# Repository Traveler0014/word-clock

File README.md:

# Word Clock 字钟项目

QLOCKTWO-style English word clock — ESP32-C5 + WS2812B (114 LEDs), built with Rust (esp-idf-svc on ESP-IDF v5.5.1), parametric 3D-printed enclosure.

QLOCKTWO 风格英文字钟：11×10 字母阵 + 4 角分钟点，ESP32-C5 + WS2812B（60灯/米），结构件 3D 打印。

**当前状态：Phase A-MVP 实机已点亮**（自检 → WiFi → SNTP → 每分钟刷新全链路跑通，2026-08）。

## 目录结构

| 路径 | 内容 |
|---|---|
| `firmware/` | Rust 固件（esp-idf-svc / std on IDF v5.5.1）+ 可宿主测试的 `wordclock-core` |
| `enclosure/` | 3D 打印结构件（OpenSCAD 参数化源码） |
| `hardware/` | 灯板 PCB（KiCad 原理图 + PCB + Gerber + 生成脚本） |
| `docs/` | 项目文档（见下） |
| `tools/` | 宿主机工具：串口嗅探、帧校验、动效实验台（`anim_lab.py`） |
| `AGENTS.md` | AI agent 快速上手指南 |

## 文档导航

| 文档 | 内容 |
|---|---|
| [docs/roadmap.md](docs/roadmap.md) | 路线图与当前进度 |
| [docs/development.md](docs/development.md) | 开发指南：环境搭建、编译烧录、日志调试、踩坑记录 |
| [docs/wiring.md](docs/wiring.md) | 接线图：供电/数据/灯链布局/验证阶段接线 |
| [docs/bom.md](docs/bom.md) | 物料清单与功率预算 |
| [docs/animation.md](docs/animation.md) | 灯板动效设计：克制的语法、状态→母题表、星场算法、α↔8bit 换算 |
| [docs/led-pcb.md](docs/led-pcb.md) | 灯板 PCB 方案评估：尺寸/pitch 决策、电学设计、与 ESP32-C5 连接 |
| [hardware/README.md](hardware/README.md) | 灯板 PCB 设计文件说明（KiCad 原理图/PCB/Gerber/生成脚本） |
| [firmware/README.md](firmware/README.md) | 固件模块结构与版本锁定 |
| [enclosure/README.md](enclosure/README.md) | 结构件参数与打印说明 |

## 快速开始

```bash
cd firmware && source env.sh                     # 环境（一次性）
cargo test -p wordclock-core --target x86_64-unknown-linux-gnu   # 逻辑层测试（宿主机）
```

编译刷写与日志调试见 [docs/development.md](docs/development.md)。

## License

[MIT](LICENSE)

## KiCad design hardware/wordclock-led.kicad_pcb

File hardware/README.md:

# hardware/ — 灯板 PCB 设计（KiCad）

把原方案的 10 行灯条 + 27 处行间飞线，替换成**单块 192×192mm 的 LED 面板 PCB**。
含**原理图 + PCB + Gerber + 预览图 + 可复现的生成脚本**。

> 方案背景与取舍见 [`../docs/led-pcb.md`](../docs/led-pcb.md)。
> 本目录是其中「方案 A：灯板 + 现有 ESP32-C5-DevKitC」的具体实现。

## 文件

| 文件 | 内容 |
|---|---|
| `wordclock-led.kicad_pro` | KiCad 工程 |
| `wordclock-led.kicad_sch` | 原理图（平坦单页 A1：114 颗灯 + 电平转换 + 电源/接口） |
| `wordclock-led.kicad_pcb` | PCB（2 层，已铺铜填充） |
| `wordclock-led-sch.pdf` | 原理图 PDF（便于评审） |
| `gen/gen_sch.py` | 原理图生成脚本（纯标准库，任意 python3） |
| `gen/gen_pcb.py` | PCB 生成脚本（需 KiCad 自带 python + pcbnew） |
| `preview/pcb_top.png` / `pcb_bottom.png` | 3D 预览 |
| `fab/*` | Gerber + 钻孔（F.Cu/B.Cu/Mask/Paste/Silk/Edge + drl + job） |

> `fab/pcba.step` 不入库（`.gitignore` 已排除）：它与 `pcba.step` 字节完全一致，
> 只是给「自洽的 fab 包」用。要直接丢给板厂/贴片厂时手动拷：`cp pcba.step fab/`。

## 板子规格

| 项 | 值 |
|---|---|
| 尺寸 / 层数 | 192.0 × 192.0 mm，2 层，1.6 mm，1oz（建议 2oz 或限制亮度） |
| 灯 | 114 × WS2812B 5050（110 字母阵 11×10 + 4 角点） |
| 灯距 pitch | **15.0 mm**（字母阵 165×150，居中留边 13.5 / 21） |
| 角点 | 距板角 7 mm（腔/窗由结构件做，φ11 / φ5） |
| 数据链 | 蛇形（行 0 左→右，奇数行反向），链尾 109 在左下；角点按周长环 110→111→112→113。**原理图用显式串联导线画出**（奇数行 `mirror y` 让 DIN/DOUT 朝向链方向，VDD/VSS 保持上下） |
| 走线 | 数据走线全程**无直角**：转弯一律 45° 倒角 |
| 电源 | 顶层 **GND 铺铜区**，底层 **+5V 平面**；每颗 LED/电容就近打过孔到 +5V |
| 去耦 | 每颗灯 1 × 100nF 0402（C1–C114），入口 1000µF + 22µF + 100nF |
| 电平转换 | U1 = 74AHCT1G125（SOT-23-5，5V 供电），输出串 R1 = 33Ω |
| 安装孔 | 4 × M3（四边中点，和原外壳螺丝位一致） |
| 丝印 | 板名、`5V IN (J2)` / `ESP32-C5 (J1)`、+5V/GND |

## 与 ESP32-C5 的连接

```
ESP32-C5-DevKitC-1                灯板 (J1)                板上
  GPIO4 ── 杜邦/JST 4pin DATA ──► J1.3 ──► U1.A ── 74AHCT1G125(5V) ──► R1(33Ω) ──► D1.DIN
  GND   ────────────────────────► J1.2/4 (GND)
  5V    ◄─────────────────────── J1.1 (仅当 JP1 短接)
                                   J2 = 5V/3A 外部电源输入（5V,5V,GND,GND）
```

| 连接器 | 引脚 | 网络 | 说明 |
|---|---|---|---|
| **J1**（接 DevKitC） | 1 | `/+5V_DEV` | 经 JP1 可选给开发板供 5V |
| | 2, 4 | `GND` | |
| | 3 | `/DIN_IN` | 来自 C5 `GPIO4` 的 3.3V 数据 |
| **J2**（电源输入） | 1, 2 | `+5V` | 5V/3A，双针并联 |
| | 3, 4 | `GND` | |
| **JP1**（焊桥） | 1–2 | `+5V` ↔ `/+5V_DEV` | **默认断开**；短接则灯板 5V 反给开发板 |

- **开发期**：DevKitC 用 USB 供电时 **JP1 保持断开**（否则双电源互灌）；两者务必共地（J1.2/4）。
- **成品**：外部 5V 接 J2，JP1 短接，由灯板同时给开发板供电，或继续让开发板独立供电。
- 数据电平：板载 74AHCT125 已做 3.3V→5V，**不要再外接电平转换**。

> 若后续要出「集成版 v2」（ESP32-C5-WROOM-1 直接上板），参考 `../docs/led-pcb.md` §5 方案 B：
> 原生 USB-Serial-JTAG（IO13/14）+ IO4(RMT) + IO1(ADC 光敏) + IO23/24(I2C)，
> 天线强烈建议用 WROOM-1U 外置，USB 控制台需改 sdkconfig。

## ⚠ 元件高度与勘误

- 正面最高元件：**C117 电解 11.5mm** > 排针 8.5mm > C116 2.52mm > 灯珠 1.61mm。
  结构件按 14mm 格栅净高设计。完整实测表见 [`../docs/pcba-heights.md`](../docs/pcba-heights.md)。
- **J1/J2 已换料**：原 BOM 的 C492419（XFCN PZ254V-12-4P）是**双排 2×2**，插不进
  `PinHeader_1x04`；已改用 **LCSC C19190970 = HDGC HDGCPH-PZ01-04**（单排 1×4，金镀），
  板面高 **8.54 mm**。
- STEP 外包络是 192×**202**（上下各 ~4.85mm 工艺边），实际板子 **192×192**。

## 固件

**无需改动**：仍 GPIO4、仍 114 颗、蛇形索引与 `wordclock-core::xy_to_index` 一致。
PCB 网络名与原理图完全一致（`/D0…/D113`、`/DOUT`、`/DIN_IN`、`/S1`、`/+5V_DEV`、`+5V`、`GND`），
所以在 KiCad 里「从原理图更新 PCB」不会断开已布好的线。

角点顺序在板上是 `110 左下 → 111 右下 → 112 右上 → 113 左上`。
固件只看「点亮前 n 颗」，功能不受影响；若想 `minute=1` 固定点某角，改 `Frame::dots()` 一行即可
（原 `docs/wiring.md` 的 110~113 标注需同步修正）。

## 校验记录

- **ERC**：0 error / 0 warning
- **DRC**：0 violation / 0 未连接；走线无直角（转弯均 45°）
- **网络一致性**：原理图 netlist 与 PCB 焊盘网络逐网比对，120 网 **0 mismatch**
- **串联链**：`/D0…/D113`、`/DOUT` 逐节校验（`D{i}.DOUT → D{i+1}.DIN`）全部正确
- **Gerber/钻孔**：`kicad-cli` 导出成功

重新校验（KiCad 10 命令行）：

```bash
kicad-cli sch erc   --severity-error wordclock-led.kicad_sch
kicad-cli pcb drc   --severity-error wordclock-led.kicad_pcb
kicad-cli pcb export gerbers -o fab/ -l "F.Cu,B.Cu,F.Mask,B.Mask,F.Paste,B.Paste,F.Silkscreen,B.Silkscreen,Edge.Cuts" wordclock-led.kicad_pcb
kicad-cli pcb export drill   -o fab/ wordclock-led.kicad_pcb
```

## 重新生成

```
hardware/
├── gen/gen_sch.py     # 任意 python3（Linux 亦可），读 KiCad 符号库
└── gen/gen_pcb.py     # 必须用 KiCad 自带 python（带 pcbnew 模块）
```

```bash
cd hardware
python3 gen/gen_sch.py                                   # 生成 .kicad_sch
"C:/Program Files/KiCad/10.0/bin/python.exe" gen/gen_pcb.py   # 生成 .kicad_pcb（含铺铜）
```

脚本里的几何参数（板尺寸、pitch、元件坐标、走线）都在文件顶部，改完全局重跑即可。
两脚本自动探测 KiCad 安装路径（Windows `D:\...` 或 WSL `/mnt/d/...`）。
每次生成 UUID 随机，故与已提交版本会有 diff，属正常。

> `gen_pcb.py` 的铺铜需要「保存→重新加载→填充→再保存」的往返：
> 无头模式下直接对新建 board 调 `ZONE_FILLER` 会崩（已在脚本内处理）。

## 打样 / 装配注意

- 2 层 192×192 已能覆盖当前电流（实测 <0.5A）；全白跑满 6.8A 时请用 2oz 或限亮。
- 每颗 5050 的 GND 焊盘**实心**连到 GND 铺铜（利于散热与载流）；返修时热风要够功率。
- C117（1000µF 直立电解）在板正面顶边（146, 11.5），高度约 12mm。
- 控制区（顶边 y≈3..19）元件在**正面**：结构件需在该处留凹槽/让位，
  或把控制区整体移到板背（+5V 平面留 keepout 即可）。见「待决」。
- 建议先打 **1 片** 验证：先只上 5V 测短路/静态电流，再用现有固件自检全链。

## 待决 / 风险

1. **"200×200"口径**：若指含外壳的成品，PCB 可再缩到 ~192→实际外框 200；当前 PCB 192 + 4mm 壁 ≈ 200×200，正好。
2. **控制区位置**：现放正面顶边，结构件要配合；若想更干净可移到背面。
3. **角点顺序**：如需 `minute=1 → 左上`，改固件映射（1 行）。
4. **散热/密封**：密封腔 + 1/4 限亮预计 OK；全白需通风。
5. **是否做集成版 v2**（C5 上板）：见 `../docs/led-pcb.md` §5。

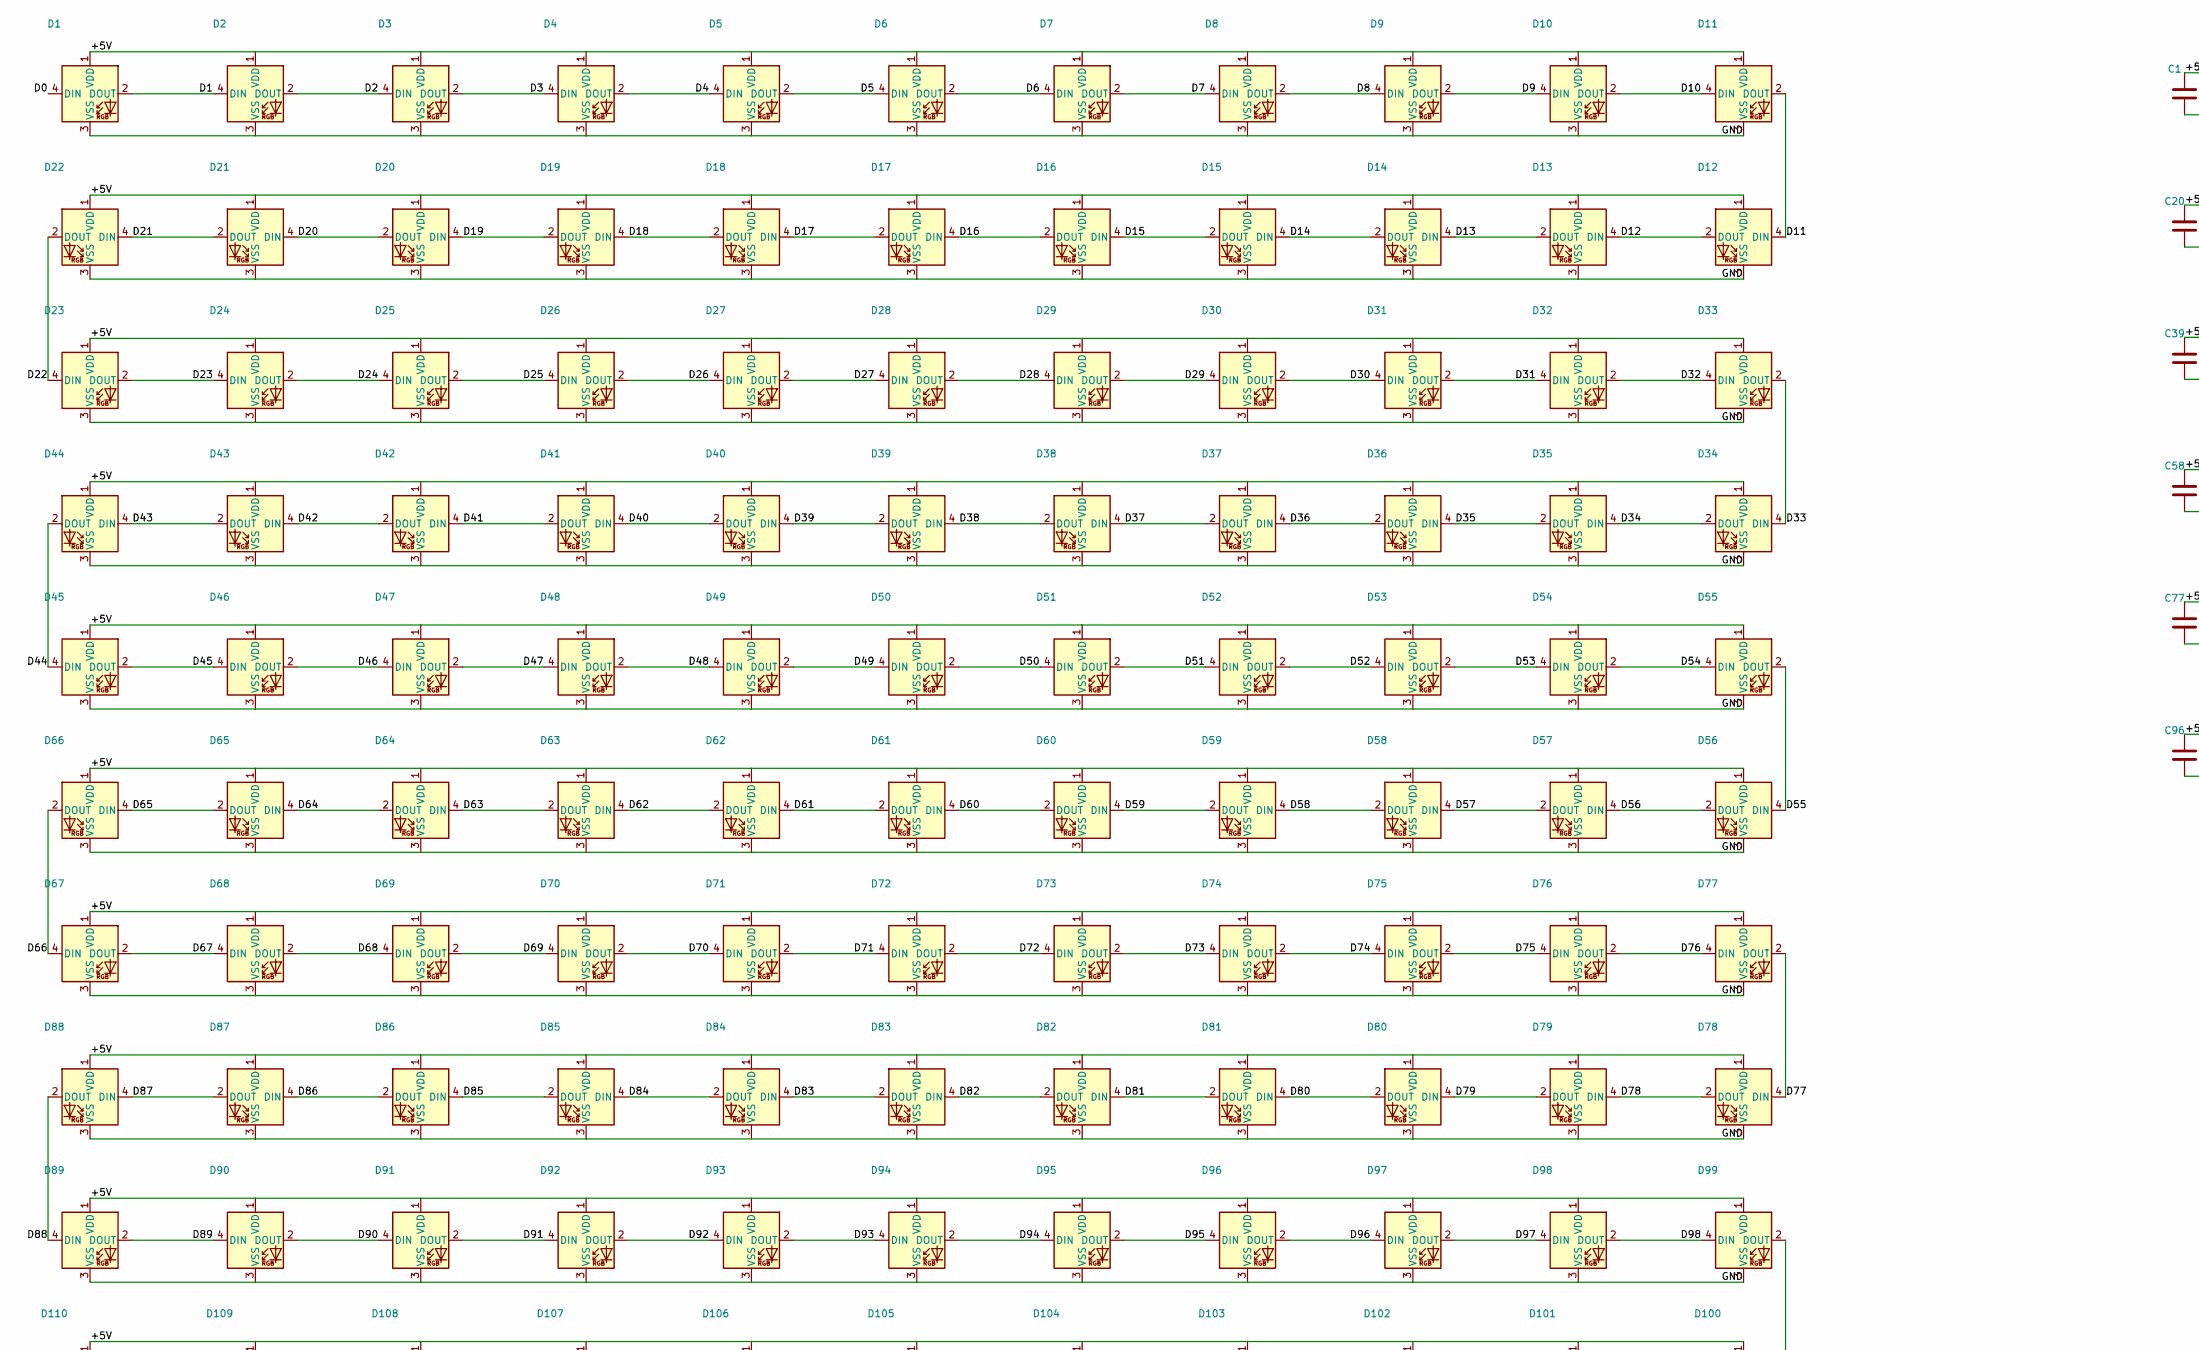
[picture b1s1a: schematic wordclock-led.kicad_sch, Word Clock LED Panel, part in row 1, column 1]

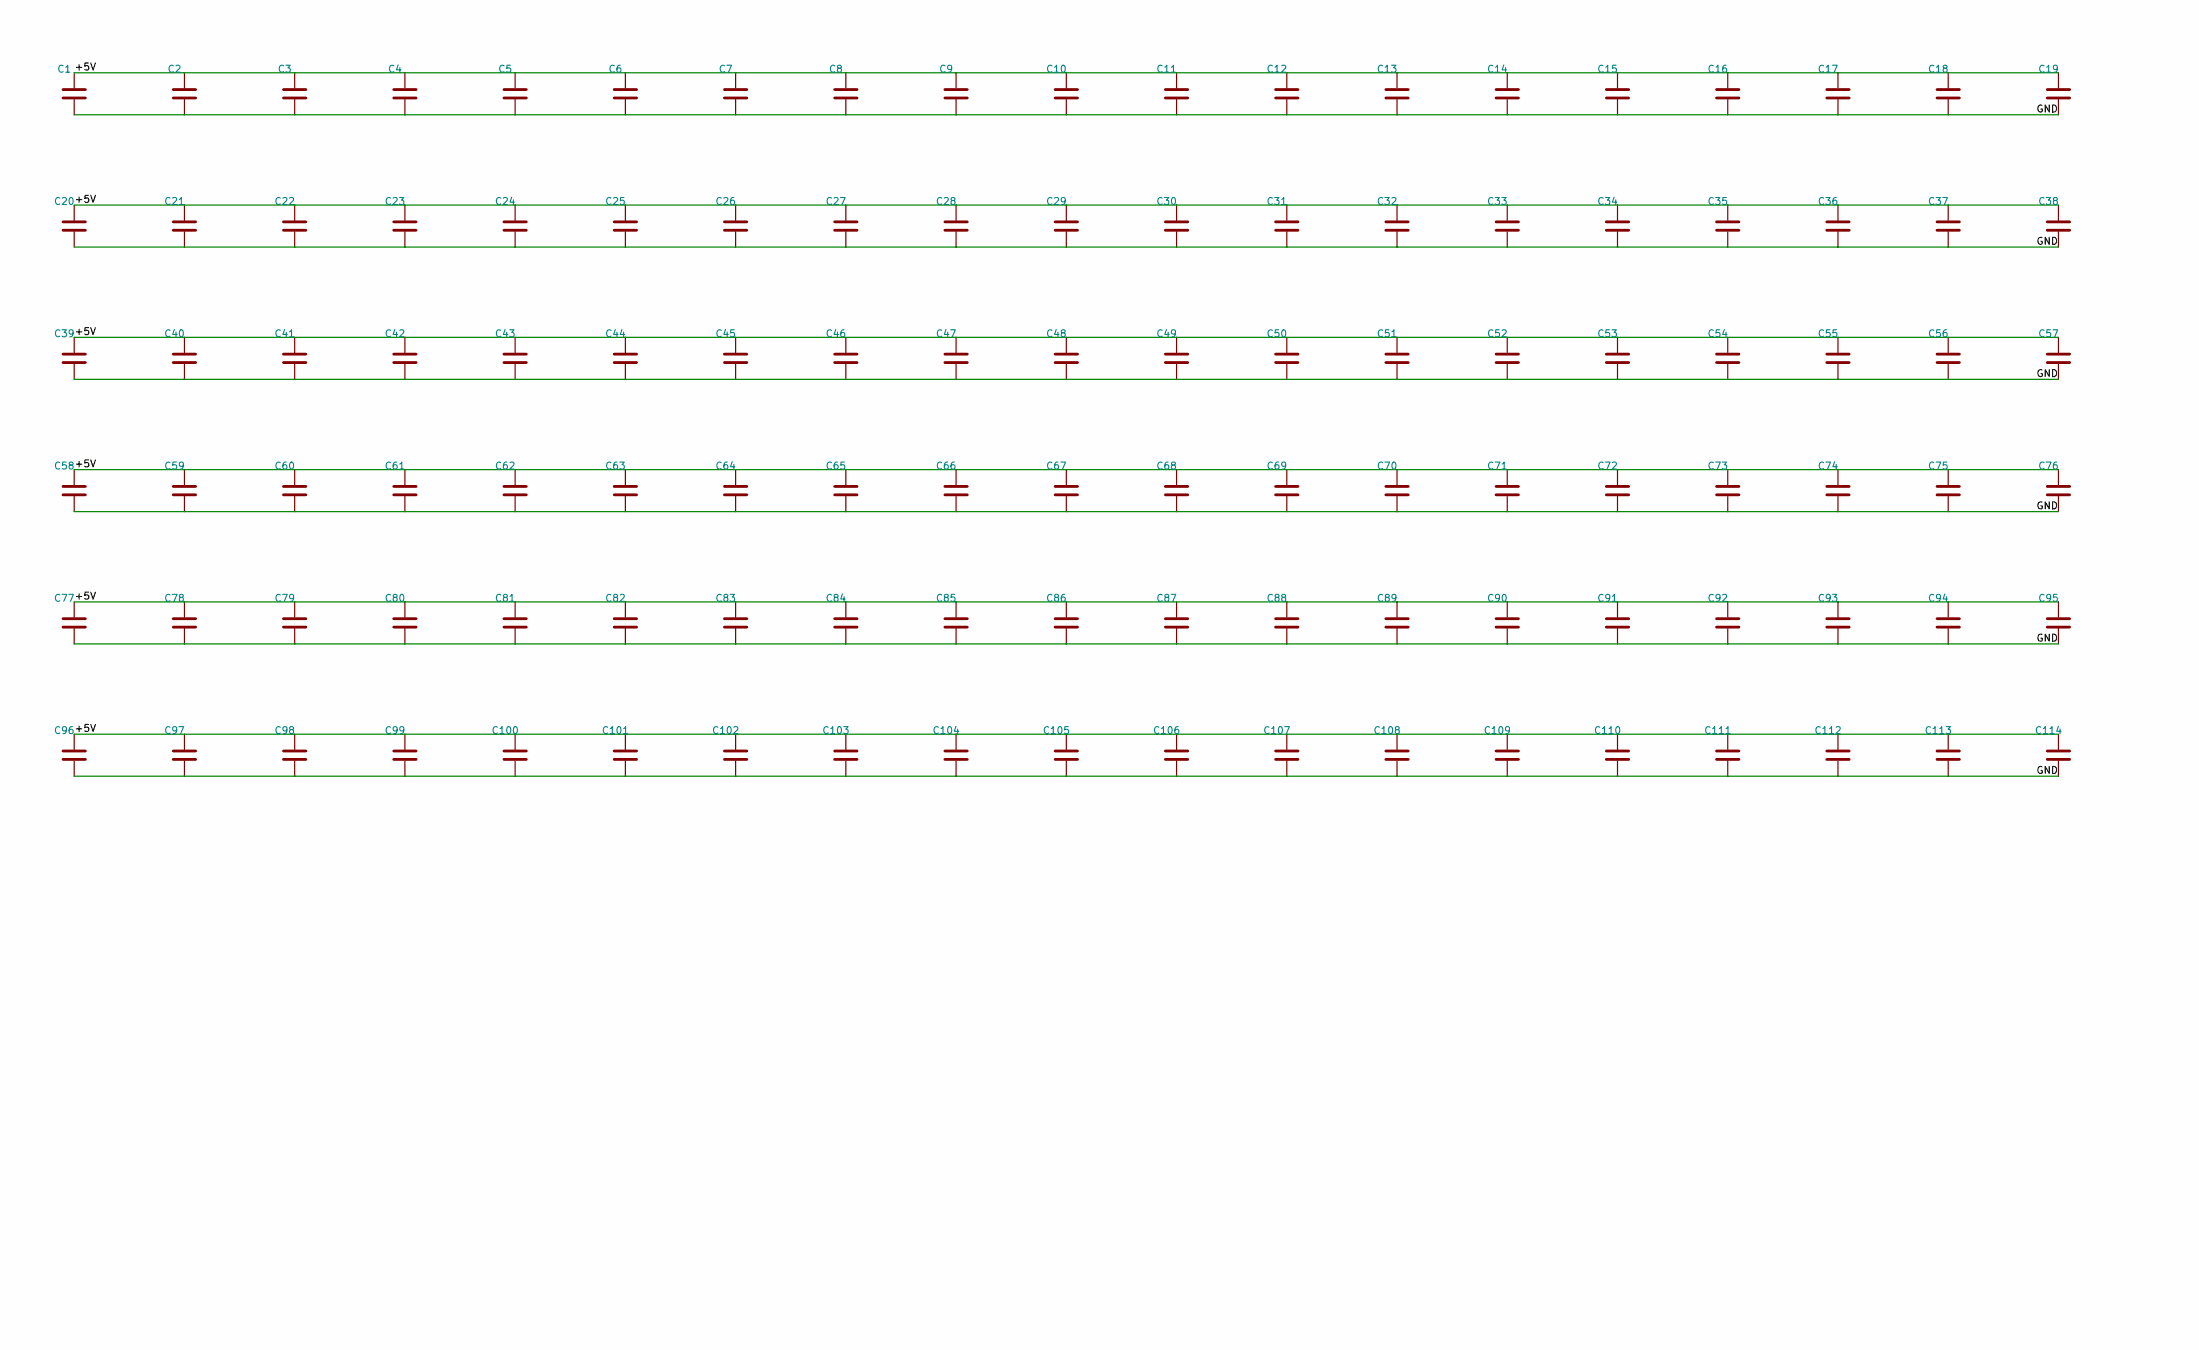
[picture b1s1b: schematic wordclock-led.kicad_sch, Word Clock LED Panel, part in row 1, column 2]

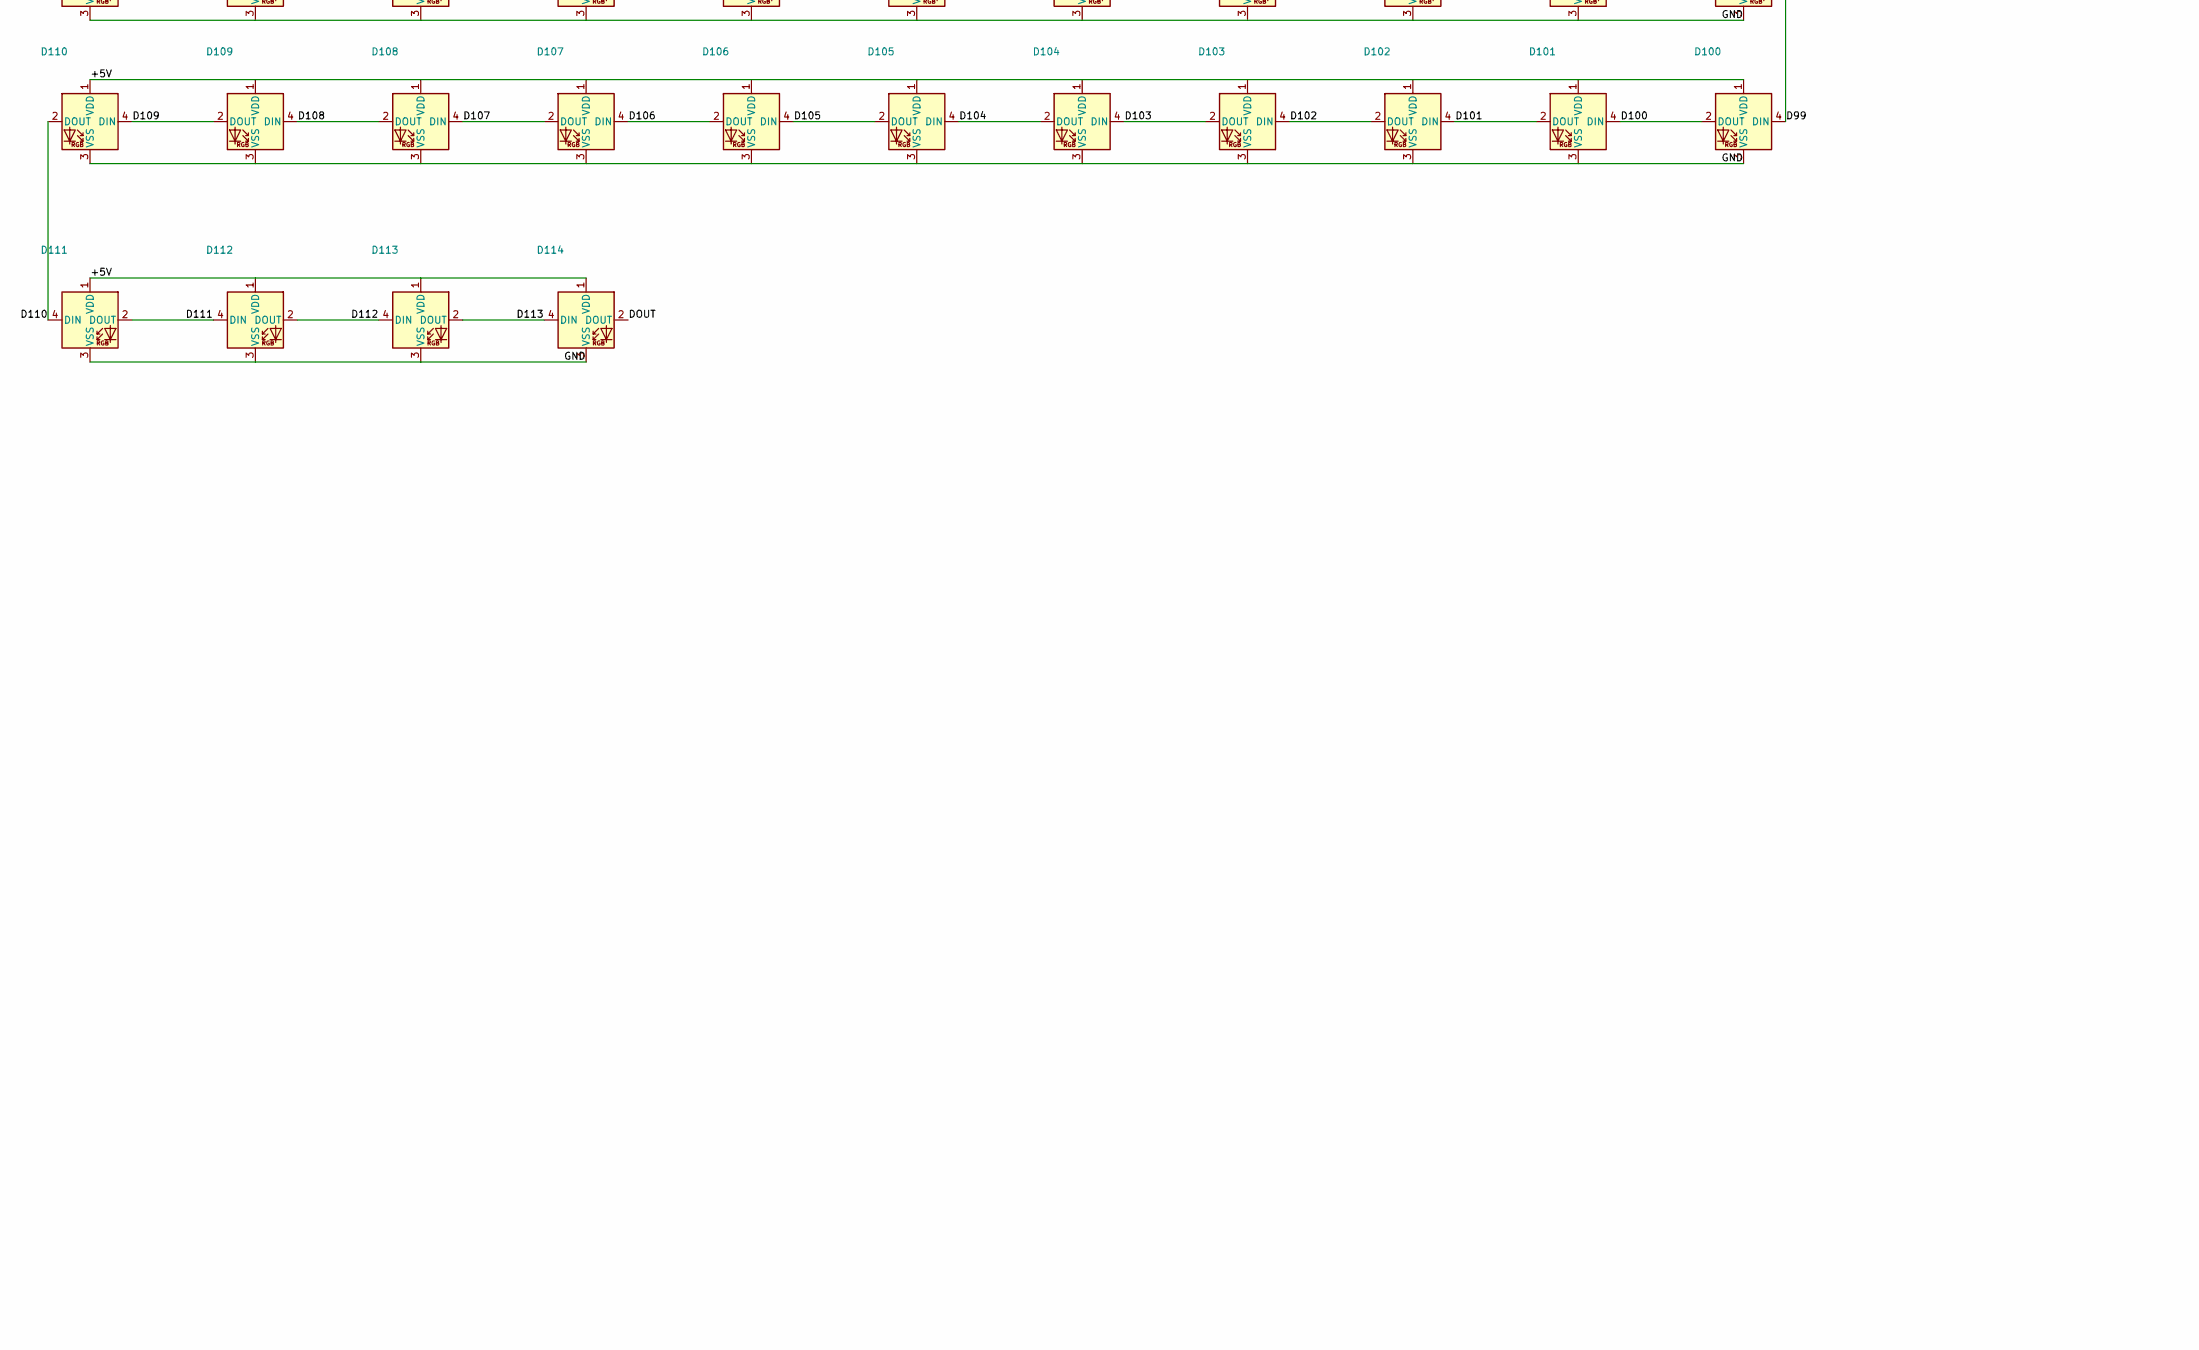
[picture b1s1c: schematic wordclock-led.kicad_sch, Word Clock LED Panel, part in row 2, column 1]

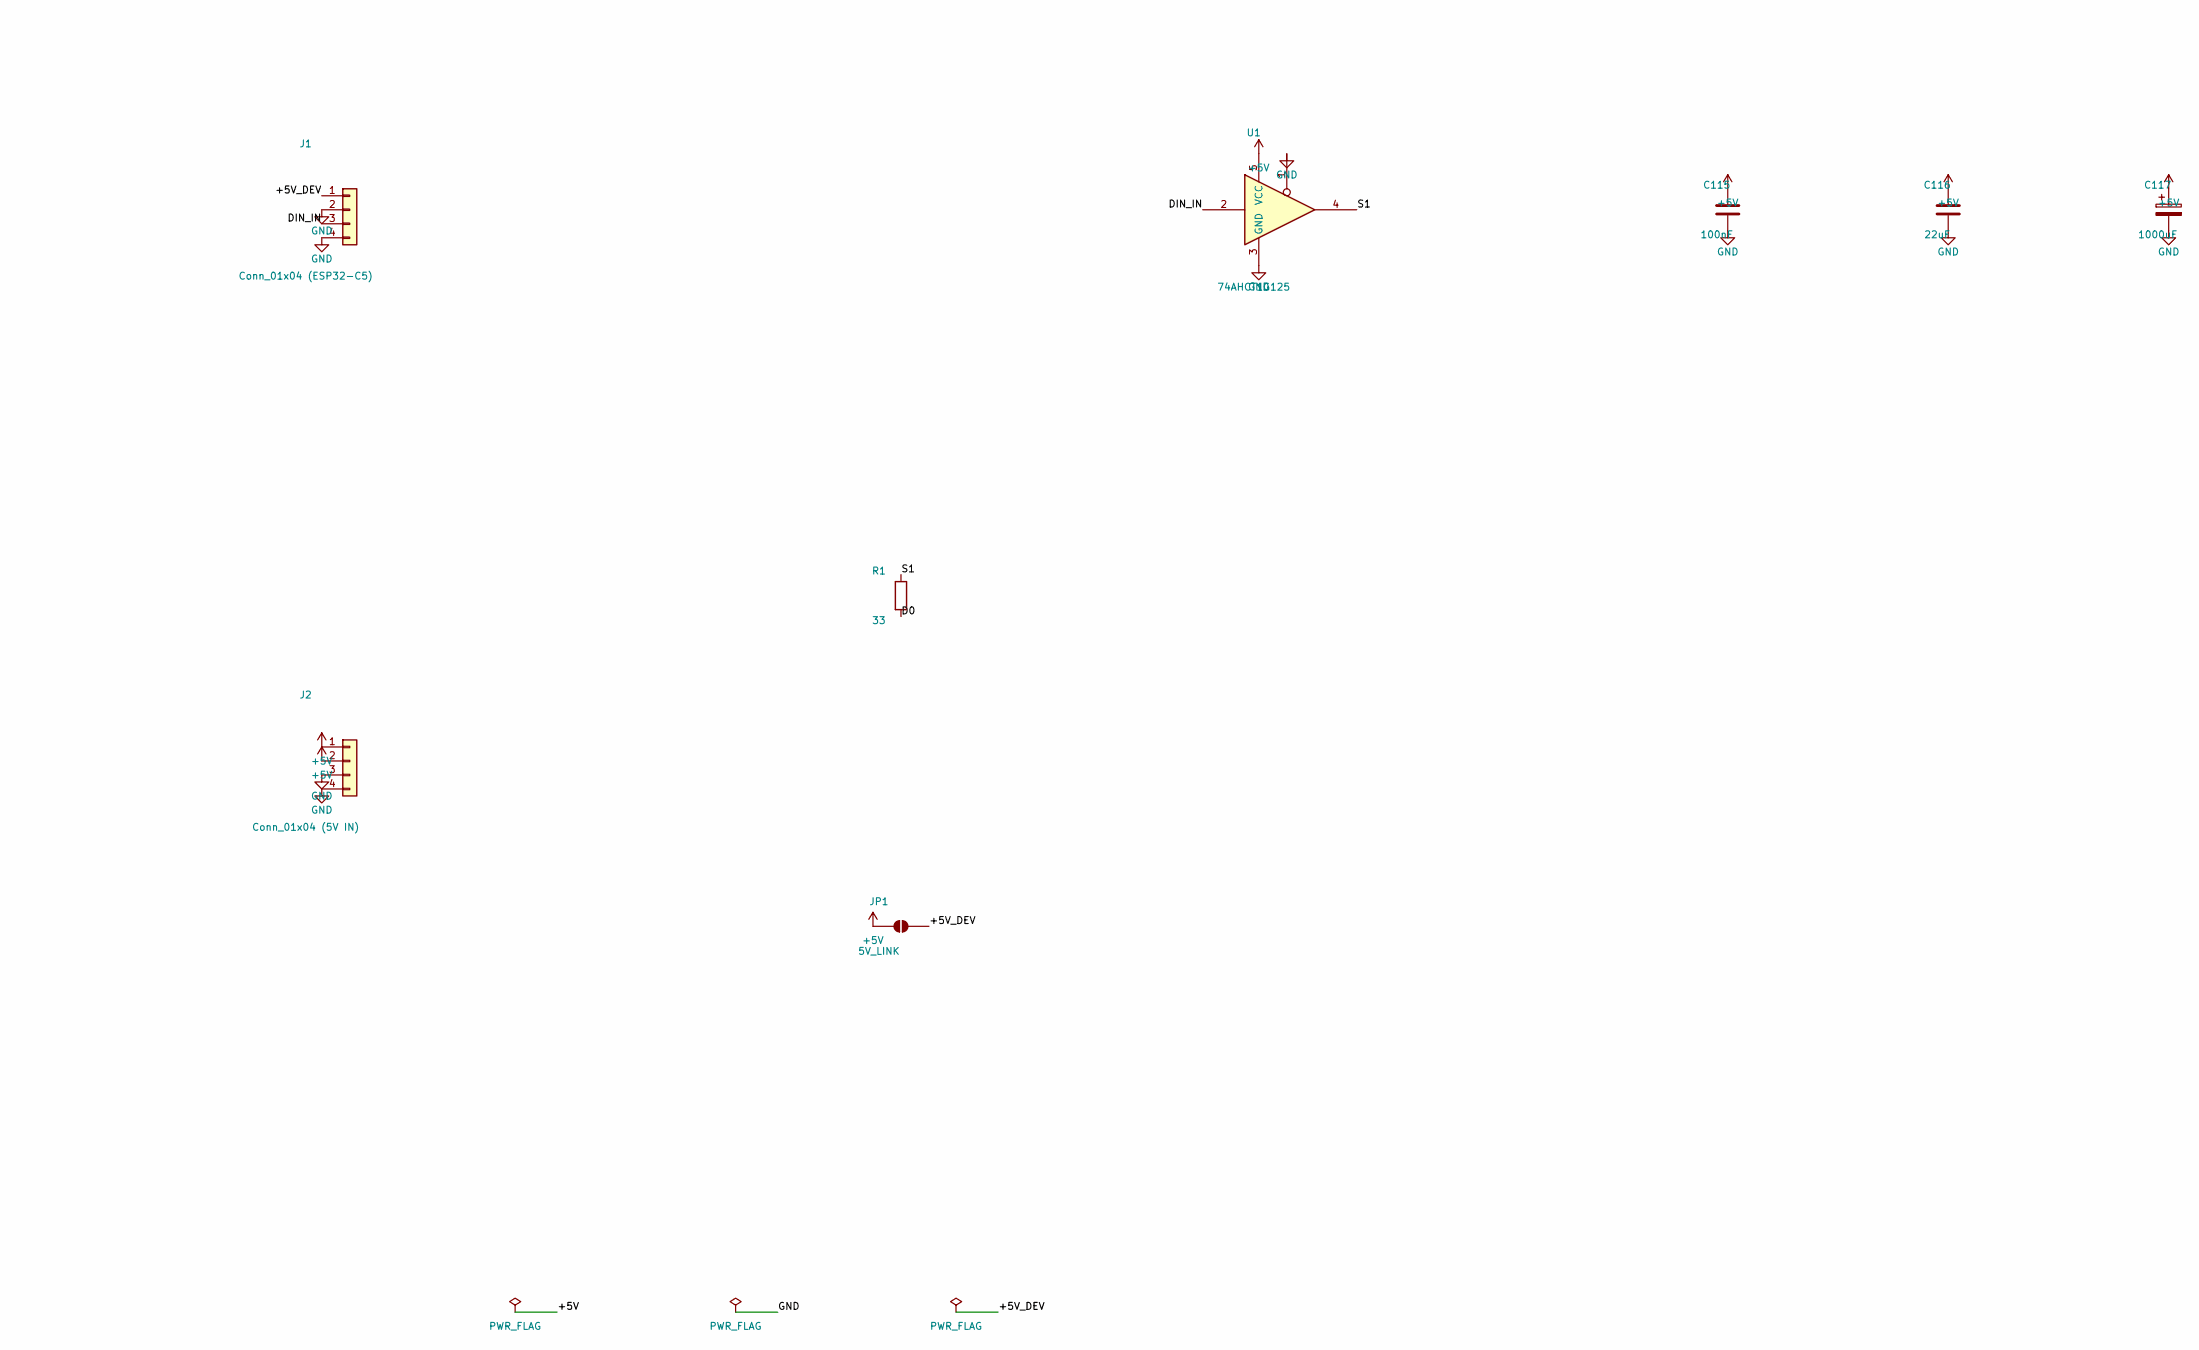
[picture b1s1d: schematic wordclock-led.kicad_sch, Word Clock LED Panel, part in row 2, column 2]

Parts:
C1, C2, C3, C4, C5, C6, C7, C8, C9, C10, C11, C12, C13, C14, C15, C16, C17, C18, C19, C20, C21, C22, C23, C24, C25, C26, C27, C28, C29, C30, C31, C32, C33, C34, C35, C36, C37, C38, C39, C40, C41, C42, C43, C44, C45, C46, C47, C48, C49, C50, C51, C52, C53, C54, C55, C56, C57, C58, C59, C60, C61, C62, C63, C64, C65, C66, C67, C68, C69, C70, C71, C72, C73, C74, C75, C76, C77, C78, C79, C80, C81, C82, C83, C84, C85, C86, C87, C88, C89, C90, C91, C92, C93, C94, C95, C96, C97, C98, C99, C100, C101, C102, C103, C104, C105, C106, C107, C108, C109, C110, C111, C112, C113, C114: 100nF; C_0402_1005Metric
C115: 100nF; C_0603_1608Metric
C116: 22uF; C_1210_3225Metric
C117: 1000uF; CP_Radial_D10.0mm_P5.00mm
D1, D2, D3, D4, D5, D6, D7, D8, D9, D10, D11, D12, D13, D14, D15, D16, D17, D18, D19, D20, D21, D22, D23, D24, D25, D26, D27, D28, D29, D30, D31, D32, D33, D34, D35, D36, D37, D38, D39, D40, D41, D42, D43, D44, D45, D46, D47, D48, D49, D50, D51, D52, D53, D54, D55, D56, D57, D58, D59, D60, D61, D62, D63, D64, D65, D66, D67, D68, D69, D70, D71, D72, D73, D74, D75, D76, D77, D78, D79, D80, D81, D82, D83, D84, D85, D86, D87, D88, D89, D90, D91, D92, D93, D94, D95, D96, D97, D98, D99, D100, D101, D102, D103, D104, D105, D106, D107, D108, D109, D110, D111, D112, D113, D114: WS2812B; LED_WS2812B_PLCC4_5.0x5.0mm_P3.2mm
J1: Conn_01x04 (ESP32-C5); PinHeader_1x04_P2.54mm_Vertical
J2: Conn_01x04 (5V IN); PinHeader_1x04_P2.54mm_Vertical
JP1: 5V_LINK; SolderJumper-2_P1.3mm_Open_RoundedPad1.0x1.5mm
R1: 33; R_0603_1608Metric
U1: 74AHCT1G125; SOT-23-5

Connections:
+5V: C1.1, C2.1, C3.1, C4.1, C5.1, C6.1, C7.1, C8.1, C9.1, C10.1, C11.1, C12.1, C13.1, C14.1, C15.1, C16.1, C17.1, C18.1, C19.1, C20.1, C21.1, C22.1, C23.1, C24.1, C25.1, C26.1, C27.1, C28.1, C29.1, C30.1, C31.1, C32.1, C33.1, C34.1, C35.1, C36.1, C37.1, C38.1, C39.1, C40.1, C41.1, C42.1, C43.1, C44.1, C45.1, C46.1, C47.1, C48.1, C49.1, C50.1, C51.1, C52.1, C53.1, C54.1, C55.1, C56.1, C57.1, C58.1, C59.1, C60.1, C61.1, C62.1, C63.1, C64.1, C65.1, C66.1, C67.1, C68.1, C69.1, C70.1, C71.1, C72.1, C73.1, C74.1, C75.1, C76.1, C77.1, C78.1, C79.1, C80.1, C81.1, C82.1, C83.1, C84.1, C85.1, C86.1, C87.1, C88.1, C89.1, C90.1, C91.1, C92.1, C93.1, C94.1, C95.1, C96.1, C97.1, C98.1, C99.1, C100.1, C101.1, C102.1, C103.1, C104.1, C105.1, C106.1, C107.1, C108.1, C109.1, C110.1, C111.1, C112.1, C113.1, C114.1, C115.1, C116.1, C117.1, D1.1 (VDD), D2.1 (VDD), D3.1 (VDD), D4.1 (VDD), D5.1 (VDD), D6.1 (VDD), D7.1 (VDD), D8.1 (VDD), D9.1 (VDD), D10.1 (VDD), D11.1 (VDD), D12.1 (VDD), D13.1 (VDD), D14.1 (VDD), D15.1 (VDD), D16.1 (VDD), D17.1 (VDD), D18.1 (VDD), D19.1 (VDD), D20.1 (VDD), D21.1 (VDD), D22.1 (VDD), D23.1 (VDD), D24.1 (VDD), D25.1 (VDD), D26.1 (VDD), D27.1 (VDD), D28.1 (VDD), D29.1 (VDD), D30.1 (VDD), D31.1 (VDD), D32.1 (VDD), D33.1 (VDD), D34.1 (VDD), D35.1 (VDD), D36.1 (VDD), D37.1 (VDD), D38.1 (VDD), D39.1 (VDD), D40.1 (VDD), D41.1 (VDD), D42.1 (VDD), D43.1 (VDD), D44.1 (VDD), D45.1 (VDD), D46.1 (VDD), D47.1 (VDD), D48.1 (VDD), D49.1 (VDD), D50.1 (VDD), D51.1 (VDD), D52.1 (VDD), D53.1 (VDD), D54.1 (VDD), D55.1 (VDD), D56.1 (VDD), D57.1 (VDD), D58.1 (VDD), D59.1 (VDD), D60.1 (VDD), D61.1 (VDD), D62.1 (VDD), D63.1 (VDD), D64.1 (VDD), D65.1 (VDD), D66.1 (VDD), D67.1 (VDD), D68.1 (VDD), D69.1 (VDD), D70.1 (VDD), D71.1 (VDD), D72.1 (VDD), D73.1 (VDD), D74.1 (VDD), D75.1 (VDD), D76.1 (VDD), D77.1 (VDD), D78.1 (VDD), D79.1 (VDD), D80.1 (VDD), D81.1 (VDD), D82.1 (VDD), D83.1 (VDD), D84.1 (VDD), D85.1 (VDD), D86.1 (VDD)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
/+5V_DEV: J1.1, JP1.2 (B)
/D0: D1.4 (DIN), R1.2
/D1: D1.2 (DOUT), D2.4 (DIN)
/D2: D2.2 (DOUT), D3.4 (DIN)
/D3: D3.2 (DOUT), D4.4 (DIN)
/D4: D4.2 (DOUT), D5.4 (DIN)
/D5: D5.2 (DOUT), D6.4 (DIN)
/D6: D6.2 (DOUT), D7.4 (DIN)
/D7: D7.2 (DOUT), D8.4 (DIN)
/D8: D8.2 (DOUT), D9.4 (DIN)
/D9: D9.2 (DOUT), D10.4 (DIN)
/D10: D10.2 (DOUT), D11.4 (DIN)
/D11: D11.2 (DOUT), D12.4 (DIN)
/D12: D12.2 (DOUT), D13.4 (DIN)
/D13: D13.2 (DOUT), D14.4 (DIN)
/D14: D14.2 (DOUT), D15.4 (DIN)
/D15: D15.2 (DOUT), D16.4 (DIN)
/D16: D16.2 (DOUT), D17.4 (DIN)
/D17: D17.2 (DOUT), D18.4 (DIN)
/D18: D18.2 (DOUT), D19.4 (DIN)
/D19: D19.2 (DOUT), D20.4 (DIN)
/D20: D20.2 (DOUT), D21.4 (DIN)
/D21: D21.2 (DOUT), D22.4 (DIN)
/D22: D22.2 (DOUT), D23.4 (DIN)
/D23: D23.2 (DOUT), D24.4 (DIN)
/D24: D24.2 (DOUT), D25.4 (DIN)
/D25: D25.2 (DOUT), D26.4 (DIN)
/D26: D26.2 (DOUT), D27.4 (DIN)
/D27: D27.2 (DOUT), D28.4 (DIN)
/D28: D28.2 (DOUT), D29.4 (DIN)
/D29: D29.2 (DOUT), D30.4 (DIN)
/D30: D30.2 (DOUT), D31.4 (DIN)
/D31: D31.2 (DOUT), D32.4 (DIN)
/D32: D32.2 (DOUT), D33.4 (DIN)
/D33: D33.2 (DOUT), D34.4 (DIN)
/D34: D34.2 (DOUT), D35.4 (DIN)
/D35: D35.2 (DOUT), D36.4 (DIN)
/D36: D36.2 (DOUT), D37.4 (DIN)
/D37: D37.2 (DOUT), D38.4 (DIN)
/D38: D38.2 (DOUT), D39.4 (DIN)
/D39: D39.2 (DOUT), D40.4 (DIN)
/D40: D40.2 (DOUT), D41.4 (DIN)
/D41: D41.2 (DOUT), D42.4 (DIN)
/D42: D42.2 (DOUT), D43.4 (DIN)
/D43: D43.2 (DOUT), D44.4 (DIN)
/D44: D44.2 (DOUT), D45.4 (DIN)
/D45: D45.2 (DOUT), D46.4 (DIN)
/D46: D46.2 (DOUT), D47.4 (DIN)
/D47: D47.2 (DOUT), D48.4 (DIN)
/D48: D48.2 (DOUT), D49.4 (DIN)
/D49: D49.2 (DOUT), D50.4 (DIN)
/D50: D50.2 (DOUT), D51.4 (DIN)
/D51: D51.2 (DOUT), D52.4 (DIN)
/D52: D52.2 (DOUT), D53.4 (DIN)
/D53: D53.2 (DOUT), D54.4 (DIN)
/D54: D54.2 (DOUT), D55.4 (DIN)
/D55: D55.2 (DOUT), D56.4 (DIN)
/D56: D56.2 (DOUT), D57.4 (DIN)
/D57: D57.2 (DOUT), D58.4 (DIN)
/D58: D58.2 (DOUT), D59.4 (DIN)
/D59: D59.2 (DOUT), D60.4 (DIN)
/D60: D60.2 (DOUT), D61.4 (DIN)
/D61: D61.2 (DOUT), D62.4 (DIN)
/D62: D62.2 (DOUT), D63.4 (DIN)
/D63: D63.2 (DOUT), D64.4 (DIN)
/D64: D64.2 (DOUT), D65.4 (DIN)
/D65: D65.2 (DOUT), D66.4 (DIN)
/D66: D66.2 (DOUT), D67.4 (DIN)
/D67: D67.2 (DOUT), D68.4 (DIN)
/D68: D68.2 (DOUT), D69.4 (DIN)
/D69: D69.2 (DOUT), D70.4 (DIN)
/D70: D70.2 (DOUT), D71.4 (DIN)
/D71: D71.2 (DOUT), D72.4 (DIN)
/D72: D72.2 (DOUT), D73.4 (DIN)
/D73: D73.2 (DOUT), D74.4 (DIN)
/D74: D74.2 (DOUT), D75.4 (DIN)
/D75: D75.2 (DOUT), D76.4 (DIN)
/D76: D76.2 (DOUT), D77.4 (DIN)
/D77: D77.2 (DOUT), D78.4 (DIN)
/D78: D78.2 (DOUT), D79.4 (DIN)
/D79: D79.2 (DOUT), D80.4 (DIN)
/D80: D80.2 (DOUT), D81.4 (DIN)
/D81: D81.2 (DOUT), D82.4 (DIN)
/D82: D82.2 (DOUT), D83.4 (DIN)
/D83: D83.2 (DOUT), D84.4 (DIN)
/D84: D84.2 (DOUT), D85.4 (DIN)
/D85: D85.2 (DOUT), D86.4 (DIN)
/D86: D86.2 (DOUT), D87.4 (DIN)
/D87: D87.2 (DOUT), D88.4 (DIN)
/D88: D88.2 (DOUT), D89.4 (DIN)
/D89: D89.2 (DOUT), D90.4 (DIN)
/D90: D90.2 (DOUT), D91.4 (DIN)
/D91: D91.2 (DOUT), D92.4 (DIN)
/D92: D92.2 (DOUT), D93.4 (DIN)
/D93: D93.2 (DOUT), D94.4 (DIN)
/D94: D94.2 (DOUT), D95.4 (DIN)
/D95: D95.2 (DOUT), D96.4 (DIN)
/D96: D96.2 (DOUT), D97.4 (DIN)
/D97: D97.2 (DOUT), D98.4 (DIN)
/D98: D98.2 (DOUT), D99.4 (DIN)
/D99: D99.2 (DOUT), D100.4 (DIN)
/D100: D100.2 (DOUT), D101.4 (DIN)
/D101: D101.2 (DOUT), D102.4 (DIN)
/D102: D102.2 (DOUT), D103.4 (DIN)
/D103: D103.2 (DOUT), D104.4 (DIN)
/D104: D104.2 (DOUT), D105.4 (DIN)
/D105: D105.2 (DOUT), D106.4 (DIN)
/D106: D106.2 (DOUT), D107.4 (DIN)
/D107: D107.2 (DOUT), D108.4 (DIN)
/D108: D108.2 (DOUT), D109.4 (DIN)
/D109: D109.2 (DOUT), D110.4 (DIN)
/D110: D110.2 (DOUT), D111.4 (DIN)
/D111: D111.2 (DOUT), D112.4 (DIN)
/D112: D112.2 (DOUT), D113.4 (DIN)
/D113: D113.2 (DOUT), D114.4 (DIN)
/DIN_IN: J1.3, U1.2
/DOUT: D114.2 (DOUT)
/S1: R1.1, U1.4
GND: C1.2, C2.2, C3.2, C4.2, C5.2, C6.2, C7.2, C8.2, C9.2, C10.2, C11.2, C12.2, C13.2, C14.2, C15.2, C16.2, C17.2, C18.2, C19.2, C20.2, C21.2, C22.2, C23.2, C24.2, C25.2, C26.2, C27.2, C28.2, C29.2, C30.2, C31.2, C32.2, C33.2, C34.2, C35.2, C36.2, C37.2, C38.2, C39.2, C40.2, C41.2, C42.2, C43.2, C44.2, C45.2, C46.2, C47.2, C48.2, C49.2, C50.2, C51.2, C52.2, C53.2, C54.2, C55.2, C56.2, C57.2, C58.2, C59.2, C60.2, C61.2, C62.2, C63.2, C64.2, C65.2, C66.2, C67.2, C68.2, C69.2, C70.2, C71.2, C72.2, C73.2, C74.2, C75.2, C76.2, C77.2, C78.2, C79.2, C80.2, C81.2, C82.2, C83.2, C84.2, C85.2, C86.2, C87.2, C88.2, C89.2, C90.2, C91.2, C92.2, C93.2, C94.2, C95.2, C96.2, C97.2, C98.2, C99.2, C100.2, C101.2, C102.2, C103.2, C104.2, C105.2, C106.2, C107.2, C108.2, C109.2, C110.2, C111.2, C112.2, C113.2, C114.2, C115.2, C116.2, C117.2, D1.3 (VSS), D2.3 (VSS), D3.3 (VSS), D4.3 (VSS), D5.3 (VSS), D6.3 (VSS), D7.3 (VSS), D8.3 (VSS), D9.3 (VSS), D10.3 (VSS), D11.3 (VSS), D12.3 (VSS), D13.3 (VSS), D14.3 (VSS), D15.3 (VSS), D16.3 (VSS), D17.3 (VSS), D18.3 (VSS), D19.3 (VSS), D20.3 (VSS), D21.3 (VSS), D22.3 (VSS), D23.3 (VSS), D24.3 (VSS), D25.3 (VSS), D26.3 (VSS), D27.3 (VSS), D28.3 (VSS), D29.3 (VSS), D30.3 (VSS), D31.3 (VSS), D32.3 (VSS), D33.3 (VSS), D34.3 (VSS), D35.3 (VSS), D36.3 (VSS), D37.3 (VSS), D38.3 (VSS), D39.3 (VSS), D40.3 (VSS), D41.3 (VSS), D42.3 (VSS), D43.3 (VSS), D44.3 (VSS), D45.3 (VSS), D46.3 (VSS), D47.3 (VSS), D48.3 (VSS), D49.3 (VSS), D50.3 (VSS), D51.3 (VSS), D52.3 (VSS), D53.3 (VSS), D54.3 (VSS), D55.3 (VSS), D56.3 (VSS), D57.3 (VSS), D58.3 (VSS), D59.3 (VSS), D60.3 (VSS), D61.3 (VSS), D62.3 (VSS), D63.3 (VSS), D64.3 (VSS), D65.3 (VSS), D66.3 (VSS), D67.3 (VSS), D68.3 (VSS), D69.3 (VSS), D70.3 (VSS), D71.3 (VSS), D72.3 (VSS), D73.3 (VSS), D74.3 (VSS), D75.3 (VSS), D76.3 (VSS), D77.3 (VSS), D78.3 (VSS), D79.3 (VSS), D80.3 (VSS), D81.3 (VSS), D82.3 (VSS), D83.3 (VSS), D84.3 (VSS), D85.3 (VSS), D86.3 (VSS)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

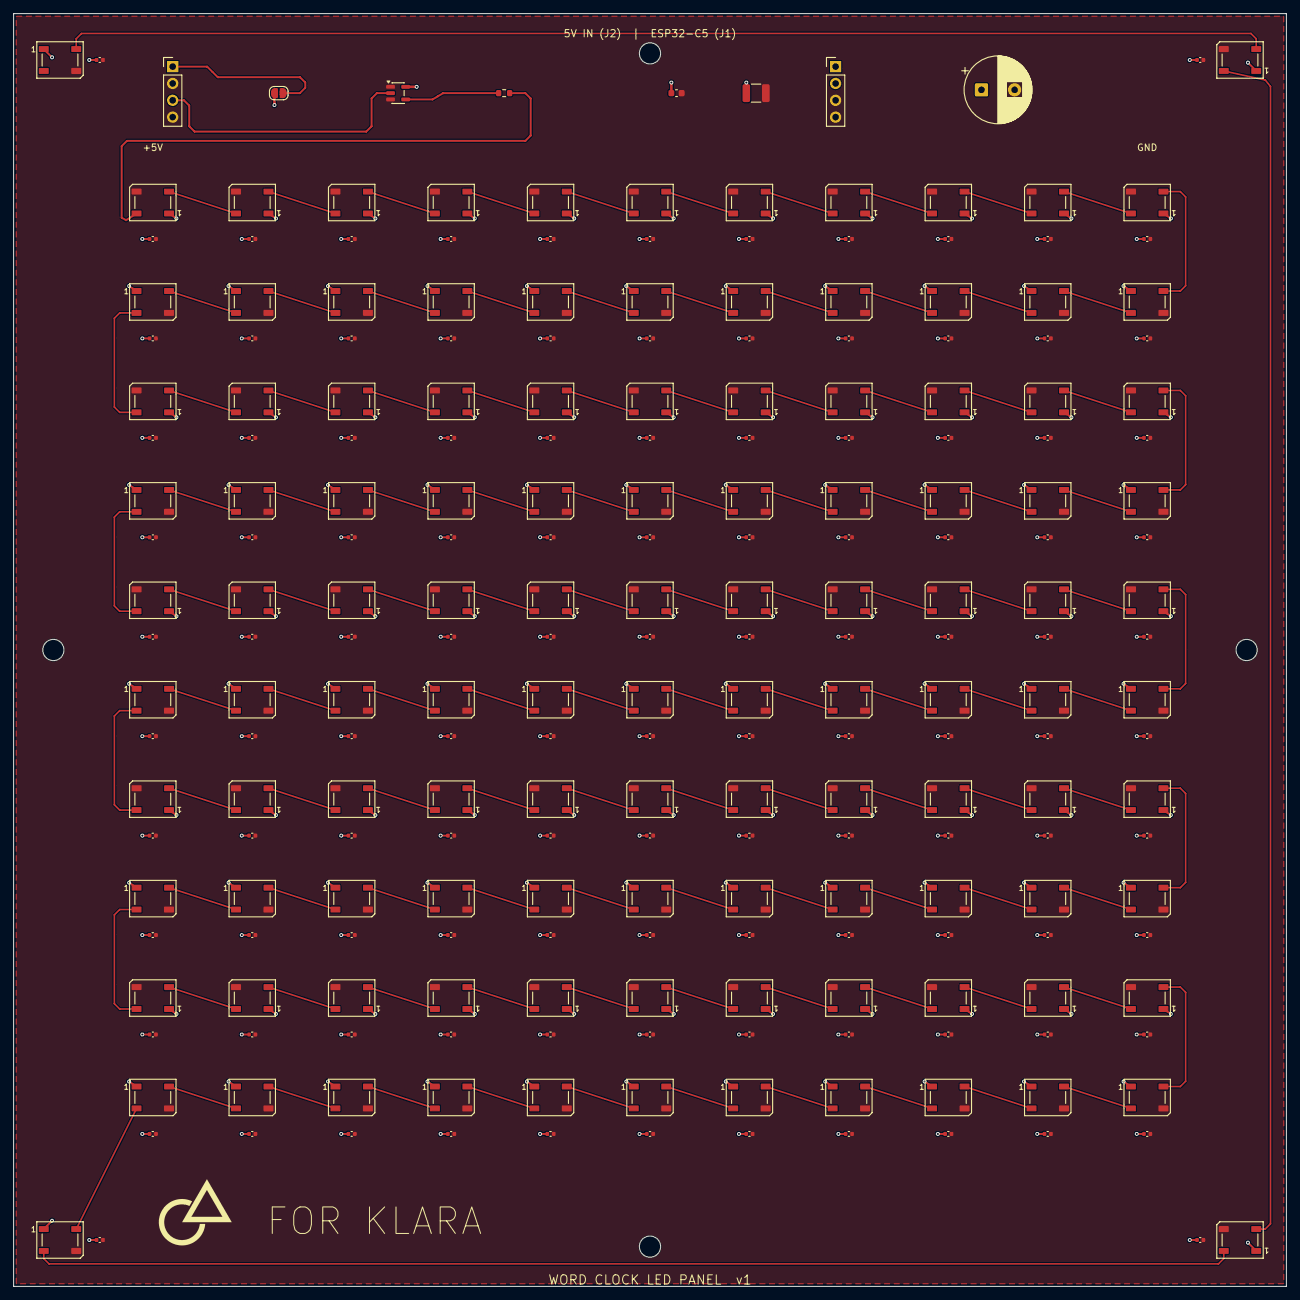
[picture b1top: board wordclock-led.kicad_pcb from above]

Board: 2 copper layers, 192.0 x 192.0 mm, 240 parts (0 on the bottom side), 119 nets.

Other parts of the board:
H1, H2, H3, H4: MountingHole; MountingHole_3.2mm_M3

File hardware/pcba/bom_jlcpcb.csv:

"Comment","Designator","Footprint","LCSC Part #"
"WS2812B-V5/W","D1,D2,D3,D4,D5,D6,D7,D8,D9,D10,D11,D12,D13,D14,D15,D16,D17,D18,D19,D20,D21,D22,D23,D24,D25,D26,D27,D28,D29,D30,D31,D32,D33,D34,D35,D36,D37,D38,D39,D40,D41,D42,D43,D44,D45,D46,D47,D48,D49,D50,D51,D52,D53,D54,D55,D56,D57,D58,D59,D60,D61,D62,D63,D64,D65,D66,D67,D68,D69,D70,D71,D72,D73,D74,D75,D76,D77,D78,D79,D80,D81,D82,D83,D84,D85,D86,D87,D88,D89,D90,D91,D92,D93,D94,D95,D96,D97,D98,D99,D100,D101,D102,D103,D104,D105,D106,D107,D108,D109,D110,D111,D112,D113,D114","LED_WS2812B_PLCC4_5.0x5.0mm","C2874885"
"100nF-0402","C1,C2,C3,C4,C5,C6,C7,C8,C9,C10,C11,C12,C13,C14,C15,C16,C17,C18,C19,C20,C21,C22,C23,C24,C25,C26,C27,C28,C29,C30,C31,C32,C33,C34,C35,C36,C37,C38,C39,C40,C41,C42,C43,C44,C45,C46,C47,C48,C49,C50,C51,C52,C53,C54,C55,C56,C57,C58,C59,C60,C61,C62,C63,C64,C65,C66,C67,C68,C69,C70,C71,C72,C73,C74,C75,C76,C77,C78,C79,C80,C81,C82,C83,C84,C85,C86,C87,C88,C89,C90,C91,C92,C93,C94,C95,C96,C97,C98,C99,C100,C101,C102,C103,C104,C105,C106,C107,C108,C109,C110,C111,C112,C113,C114","C_0402_1005Metric","C1525"
"PinHeader-1x4","J1,J2","PinHeader_1x04_P2.54mm_Vertical","C19190970"
"100nF-0603","C115","C_0603_1608Metric","C14663"
"22uF-1210","C116","C_1210_3225Metric","C52306"
"1000uF-16V","C117","CP_Radial_D10.0mm_P5.00mm","C525818"
"33R-0603","R1","R_0603_1608Metric","C23140"
"74AHCT1G125","U1","SOT-23-5","C52140417"
